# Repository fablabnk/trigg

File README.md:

A low-cost, through-hole version of the Hack Club Sprig - to be presented as a not-for-profit kit and workshop at this year's Chaos Computer Congress in Hamburg (38C3)

See [here](https://github.com/hackclub/sprig/blob/main/README.md) for the original project documentation

Added 3D models (stl and f3d) for the console to [case_3d branch](https://github.com/fablabnk/trigg/blob/case_3d/case_3dprint)

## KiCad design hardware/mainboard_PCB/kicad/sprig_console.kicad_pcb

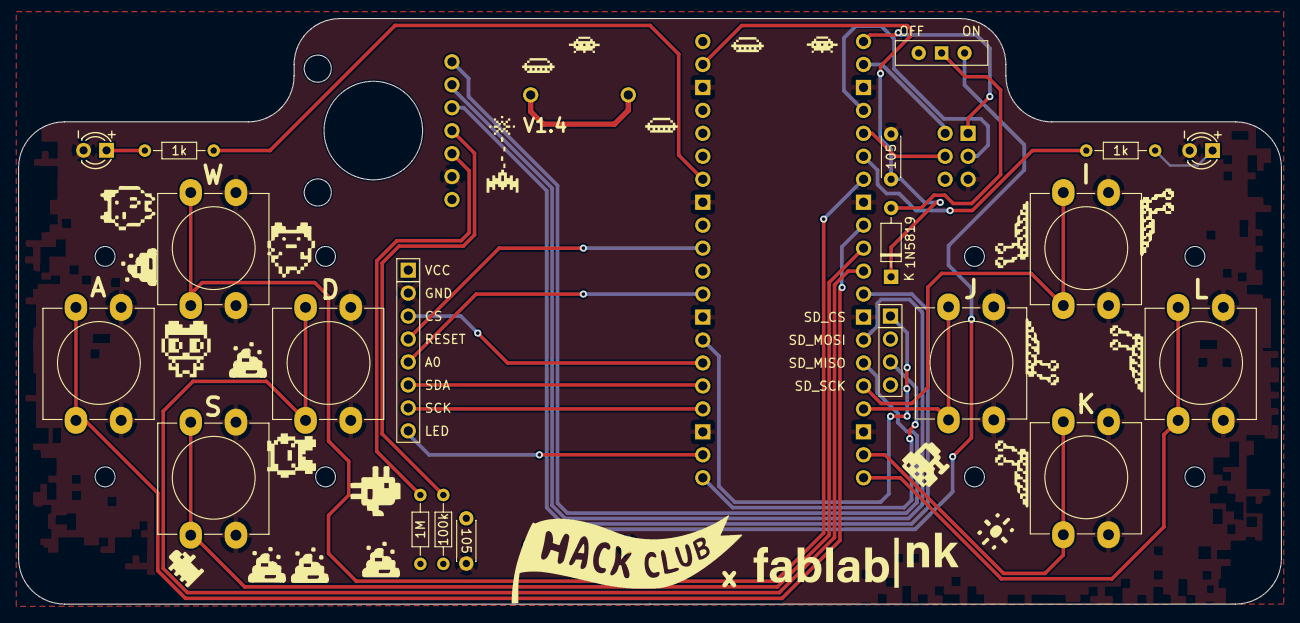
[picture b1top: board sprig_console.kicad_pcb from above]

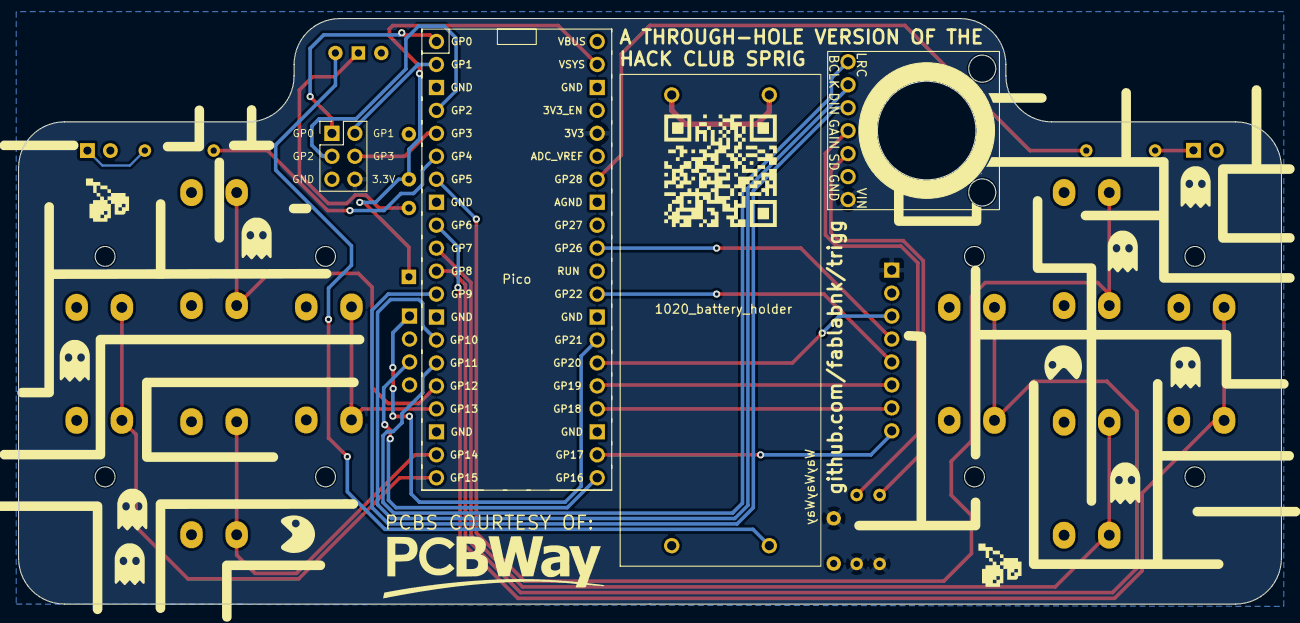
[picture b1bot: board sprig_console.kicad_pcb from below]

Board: 2 copper layers, 139.7 x 64.8 mm, 24 parts (5 on the bottom side), 35 nets.

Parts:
C1, C4: 1uF; C_Disc_D4.3mm_W1.9mm_P5.00mm
D1: R_LED; LED_3mm_C1A2_Polarity_Indicator
D2: L_LED; LED_3mm_C1A2_Polarity_Indicator
D3: 1N5819; D_DO-35_SOD27_P7.62mm_Horizontal
J1: 1020_battery_holder; 1022
J2: Conn_PinHeader_2x03_P2.54mm_Vertical_SMD; PinHeader_2x03_P2.54mm_Vertical
LS1: Speaker; 1W_8Ohm_Speaker
R1: 1M; R_Axial_DIN0204_L3.6mm_D1.6mm_P7.62mm_Horizontal
R2: 100k; R_Axial_DIN0204_L3.6mm_D1.6mm_P7.62mm_Horizontal
R3, R4: 1k; R_Axial_DIN0204_L3.6mm_D1.6mm_P7.62mm_Horizontal
SW1: W; SW_PUSH-12mm_Wuerth-430476085716
SW2: A; SW_PUSH-12mm_Wuerth-430476085716
SW3: S; SW_PUSH-12mm_Wuerth-430476085716
SW4: D; SW_PUSH-12mm_Wuerth-430476085716
SW5: I; SW_PUSH-12mm_Wuerth-430476085716
SW6: J; SW_PUSH-12mm_Wuerth-430476085716
SW7: K; SW_PUSH-12mm_Wuerth-430476085716
SW8: L; SW_PUSH-12mm_Wuerth-430476085716
SW9: Slideswitch; SW_Slide-03_Wuerth-WS-SLTV_10x2.5x6.4_P2.54mm
U1: Adafruit_TFT_ST7735; Generic_1.8Inch_TFT_120x160
U2: MAX98357AETE+; Max98357A_ClassD_I2S_Mono_Amp_BreakoutBoard
U5: Pico; RPi_Pico_SMD_TH_mod

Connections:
+3V3: C1.1, J2.6, R1.1, R2.1, U1.9 (VCC), U2.7 (Vin), U5.36 (3V3)
BCLK: U2.2 (BCLK), U5.14 (GPIO10)
BTN_A: SW2.1, U5.9 (GPIO6)
BTN_D: SW4.1, U5.11 (GPIO8)
BTN_I: SW5.1, U5.16 (GPIO12)
BTN_J: SW6.1, U5.17 (GPIO13)
BTN_K: SW7.1, U5.19 (GPIO14)
BTN_L: SW8.1, U5.20 (GPIO15)
BTN_S: SW3.1, U5.10 (GPIO7)
BTN_W: SW1.1, U5.7 (GPIO5)
CARD_CS: U1.6 (CARD_CS), U5.27 (GPIO21)
DIN: U2.3 (DIN), U5.12 (GPIO9)
D/C: U1.7 (D/C), U5.29 (GPIO22)
GND: C1.2, C4.2, D1.1 (K), D2.1 (K), J1.1, J2.5, SW1.2, SW2.2, SW3.2, SW4.2, SW5.2, SW6.2, SW7.2, SW8.2, U1.10 (GND), U2.6 (GND), U5.3 (GND), U5.8 (GND), U5.13 (GND), U5.18 (GND), U5.23 (GND), U5.28 (GND), U5.33 (AGND), U5.38 (GND)
GPIO0: J2.1, U5.1 (GPIO0)
GPIO1: J2.2, U5.2 (GPIO1)
GPIO2: J2.3, U5.4 (GPIO2)
GPIO3: J2.4, U5.5 (GPIO3)
LED_L: R4.1, U5.34 (GPIO28_ADC2)
LED_R: R3.1, U5.6 (GPIO4)
LITE: U1.1 (LITE), U5.22 (GPIO17)
LRCLK: U2.1 (LRC), U5.15 (GPIO11)
MISO: U1.2 (MISO), U5.21 (GPIO16)
MOSI: U1.4 (MOSI), U5.25 (GPIO19)
unnamed: D1.2 (A), R3.2
unnamed: D2.2 (A), R4.2
unnamed: D3.2 (A), SW9.2 (B)
unnamed: C4.1, D3.1 (K), U5.39 (VSYS)
unnamed: J1.2, J1.3
unnamed: J1.4, SW9.3 (C)
unnamed: R2.2, U2.4 (GAIN)
unnamed: R1.2, U2.5 (SD)
RESET: U1.8 (RESET), U5.31 (GPIO26_ADC0)
SCK: U1.3 (SCK), U5.24 (GPIO18)
TFT_CS: U1.5 (TFT_CS), U5.26 (GPIO20)

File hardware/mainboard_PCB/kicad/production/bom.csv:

Designator,Footprint,Quantity,Value,LCSC Part #
"_8, _7, _6, _5, _4, _3, _2, ",,8,,
"C1, C4",C_Disc_D4.3mm_W1.9mm_P5.00mm,2,1uF,
D1,LED_3mm_C1A2_Polarity_Indicator,1,R_LED,
D2,LED_3mm_C1A2_Polarity_Indicator,1,L_LED,
D3,D_DO-35_SOD27_P7.62mm_Horizontal,1,1N5819,
J1,1022,1,1020_battery_holder,
J2,PinHeader_2x03_P2.54mm_Vertical,1,Conn_PinHeader_2x03_P2.54mm_Vertical_SMD,
LS1,1W_8Ohm_Speaker,1,Speaker,
R1,R_Axial_DIN0204_L3.6mm_D1.6mm_P7.62mm_Horizontal,1,1M,
R2,R_Axial_DIN0204_L3.6mm_D1.6mm_P7.62mm_Horizontal,1,100k,
"R3, R4",R_Axial_DIN0204_L3.6mm_D1.6mm_P7.62mm_Horizontal,2,1k,
SW1,SW_PUSH-12mm_Wuerth-430476085716,1,W,
SW2,SW_PUSH-12mm_Wuerth-430476085716,1,A,
SW3,SW_PUSH-12mm_Wuerth-430476085716,1,S,
SW4,SW_PUSH-12mm_Wuerth-430476085716,1,D,
SW5,SW_PUSH-12mm_Wuerth-430476085716,1,I,
SW6,SW_PUSH-12mm_Wuerth-430476085716,1,J,
SW7,SW_PUSH-12mm_Wuerth-430476085716,1,K,
SW8,SW_PUSH-12mm_Wuerth-430476085716,1,L,
SW9,SW_Slide-03_Wuerth-WS-SLTV_10x2.5x6.4_P2.54mm,1,Slideswitch,
U1,Generic_1.8Inch_TFT_120x160,1,Adafruit_TFT_ST7735,
U2,Max98357A_ClassD_I2S_Mono_Amp_BreakoutBoard,1,MAX98357AETE+,
U5,RPi_Pico_SMD_TH_mod,1,Pico,

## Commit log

2024-11-07 resdesign of KiCad board file to a fully through hole version
2024-11-07 README update
2024-11-09 board ready for v1.0 production at jlcpcb
2024-11-29 add trigg case v0.1
2024-11-30 add 3d case image
2024-11-30 Update README.md
    added mention of then new case_3d branch to readme
2024-12-01 v1.1 board design complete for 38C3
2025-01-06 minremoved 38C3 logo from silkscreening for V1.2 to order next round of PCBs
2025-01-07 corrected capacitor silkscreening error, was 104 should be 105 for 1uf capacitor
2025-01-08 replaced 38C3 logo with fablabnk logo
2025-03-05 added correctly scaled combo .svg file for laser cut back covers
2025-04-04 finished PCB redesign V1.3 for Amaze festival
2025-11-23 Created v1.4 for 39C3
